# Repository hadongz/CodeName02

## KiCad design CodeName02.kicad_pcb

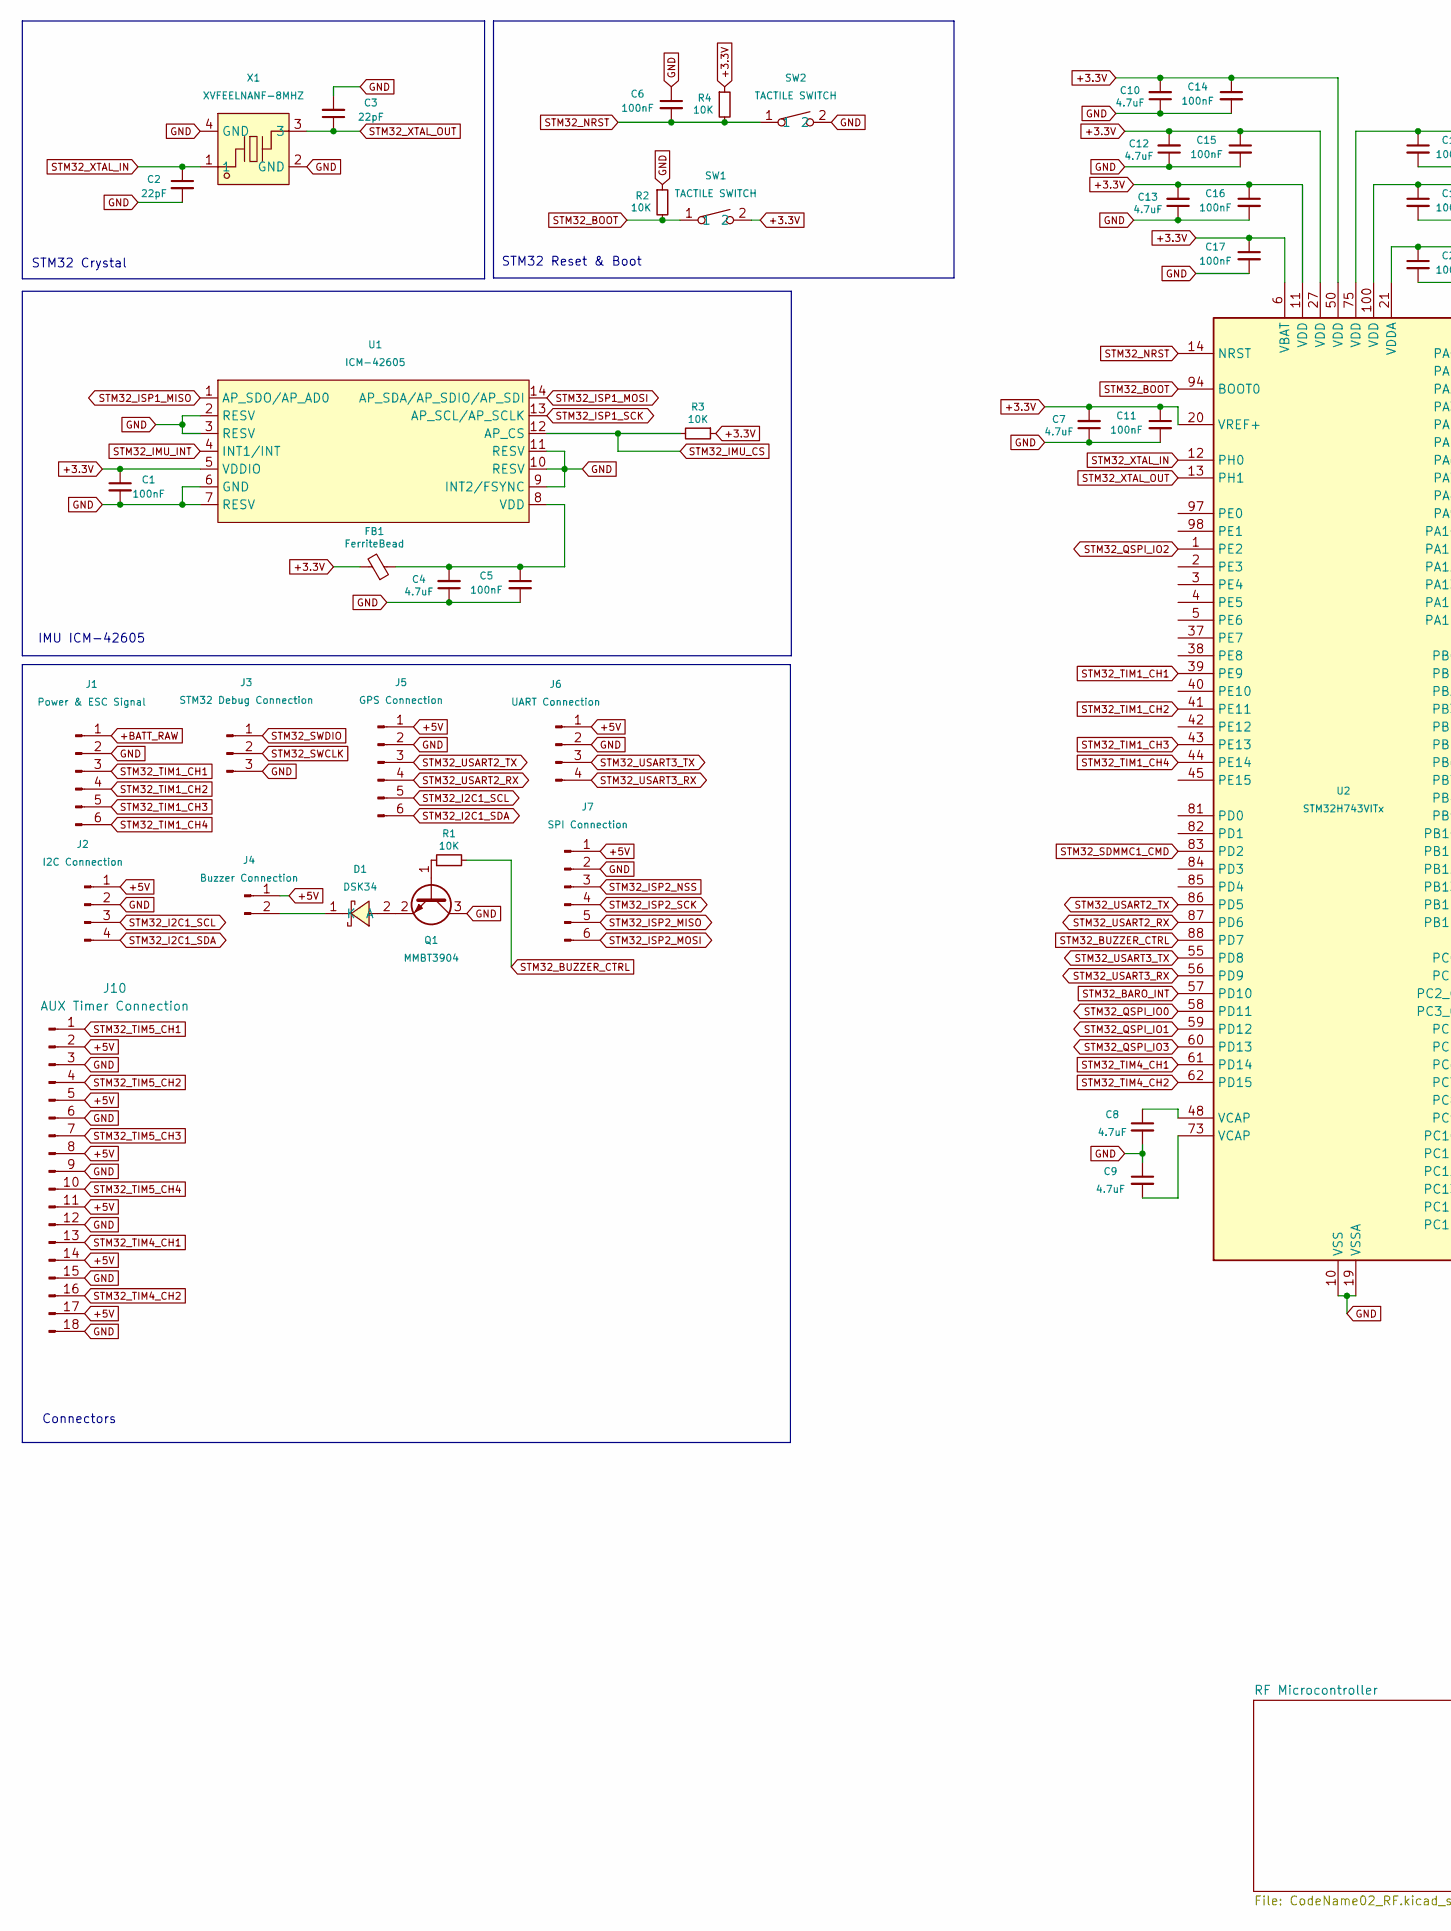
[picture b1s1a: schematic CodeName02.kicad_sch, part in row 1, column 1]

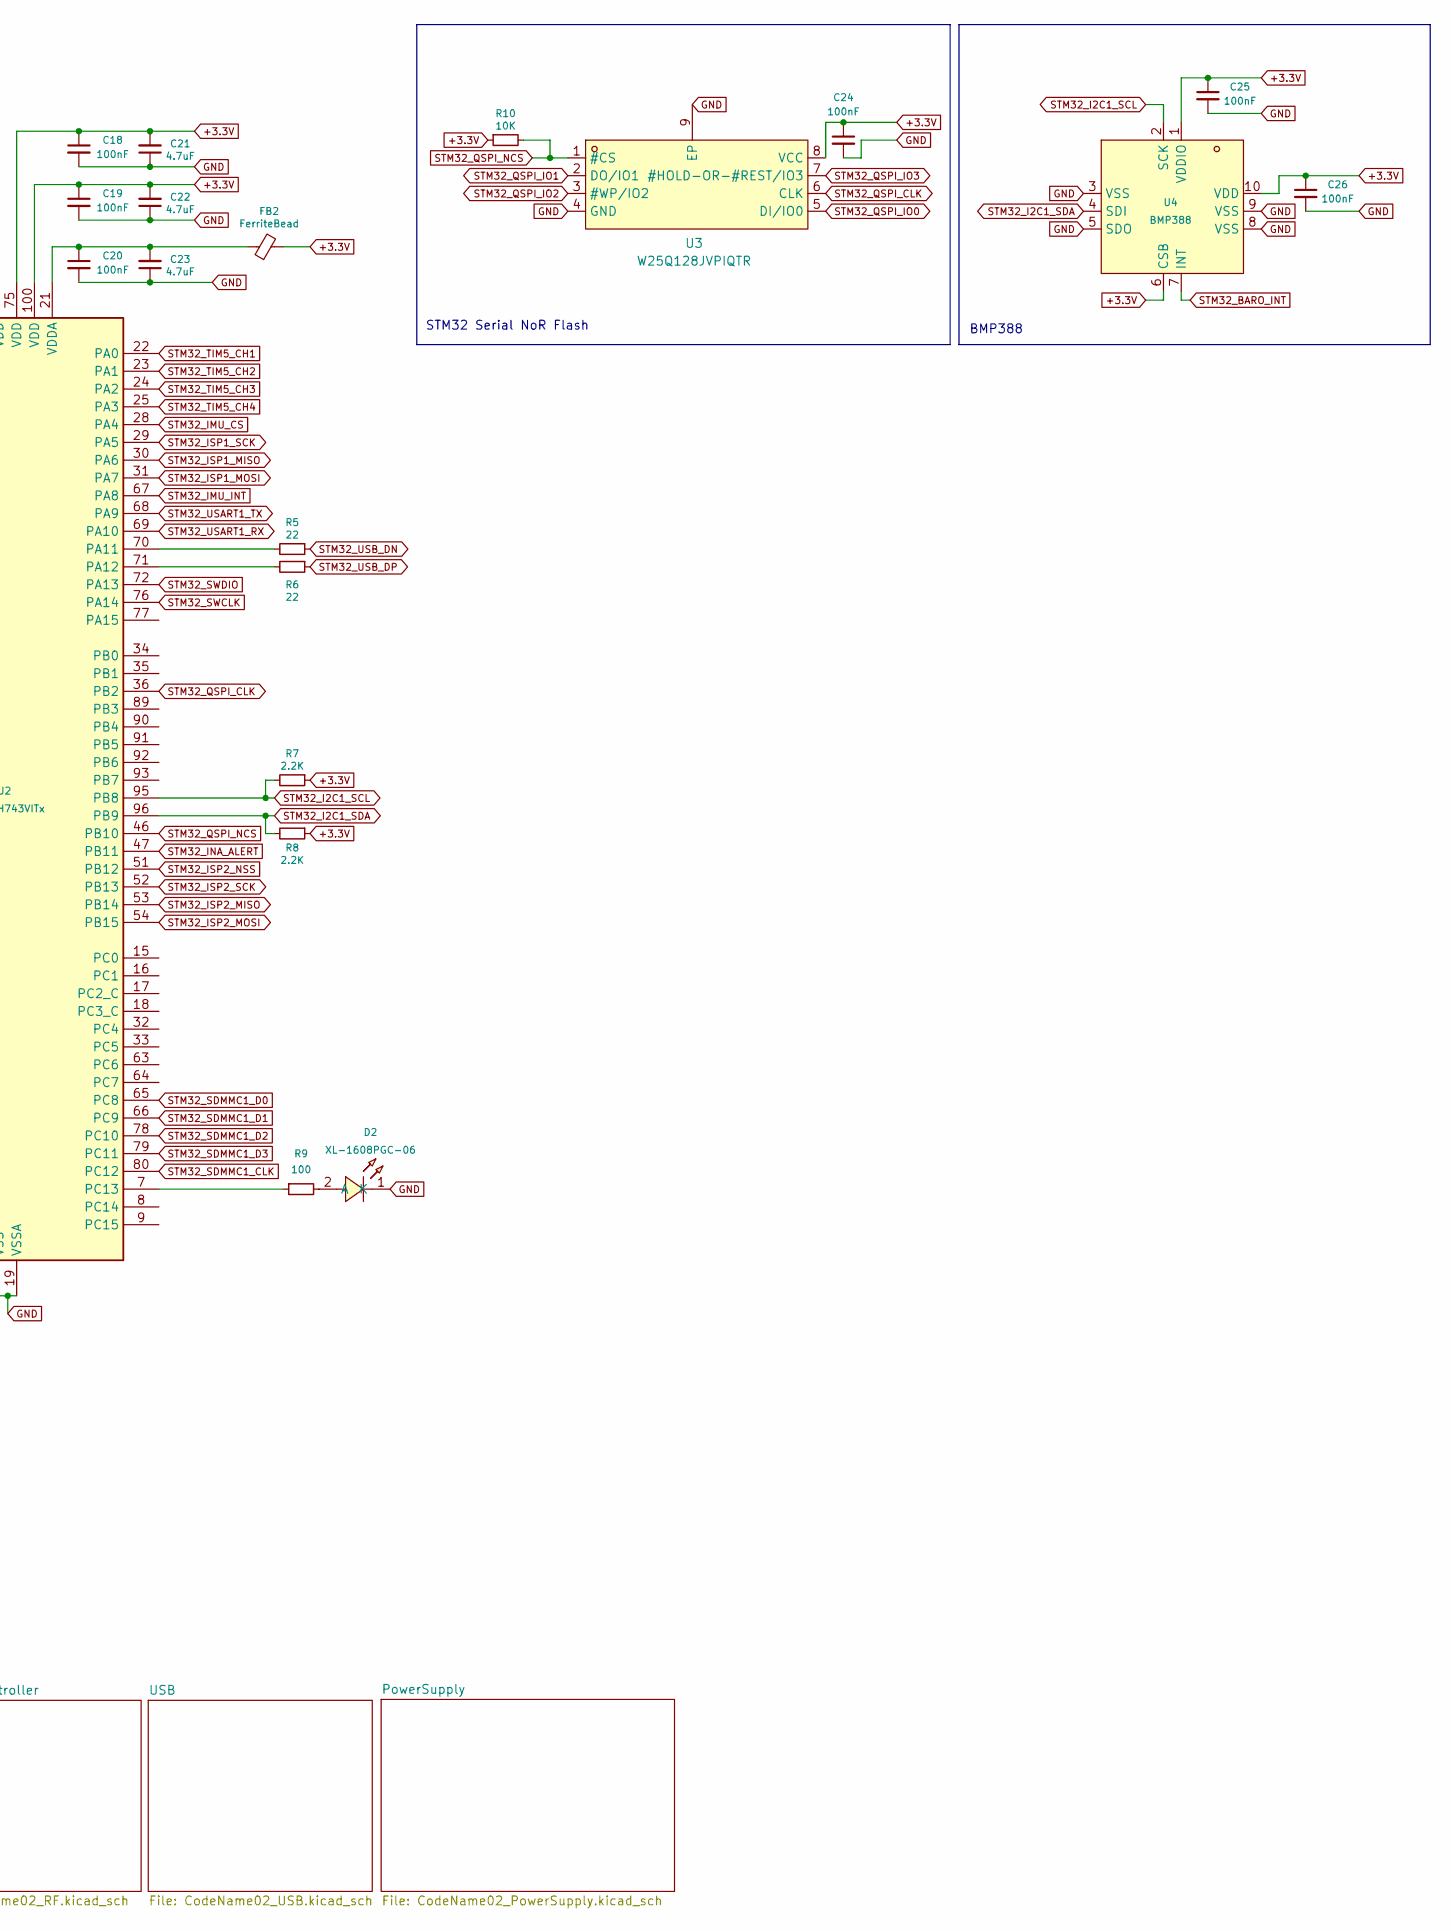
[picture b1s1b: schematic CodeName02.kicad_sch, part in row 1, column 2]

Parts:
C1, C5, C6, C11, C14, C15, C16, C17, C18, C19, C20, C24, C25, C26: 100nF; C_0603_1608Metric
C2, C3: 22pF; C_0603_1608Metric
C4, C7, C8, C9, C10, C12, C13, C21, C22, C23: 4.7uF; C_0603_1608Metric
D1: DSK34; SOD-123FL_L2.7-W1.8-LS3.8-RD; LCSC Part C727076
D2: XL-1608PGC-06; LED0603-RD_GREEN; LCSC Part C7371905
FB1, FB2: FerriteBead; L_0603_1608Metric
J1: Power & ESC Signal; JST_GH_SM06B-GHS-TB_1x06-1MP_P1.25mm_Horizontal
J2: I2C Connection; JST_GH_BM04B-GHS-TBT_1x04-1MP_P1.25mm_Vertical
J3: STM32 Debug Connection; PinHeader_1x03_P2.54mm_Vertical_Custom
J4: Buzzer Connection; JST_GH_SM02B-GHS-TB_1x02-1MP_P1.25mm_Horizontal
J5: GPS Connection; JST_GH_SM06B-GHS-TB_1x06-1MP_P1.25mm_Horizontal
J6: UART Connection; JST_GH_SM04B-GHS-TB_1x04-1MP_P1.25mm_Horizontal
J7: SPI Connection; JST_GH_SM06B-GHS-TB_1x06-1MP_P1.25mm_Horizontal
J10: AUX Timer Connection; PinHeader_3Row_Custom
Q1: MMBT3904; SOT-23
R1, R2, R3, R4, R10: 10K; R_0603_1608Metric
R5, R6: 22; R_0603_1608Metric
R7, R8: 2.2K; R_0603_1608Metric
R9: 100; R_0603_1608Metric
SW1, SW2: TACTILE SWITCH; KEY-SMD_L4.0-W3.0-LS4.9-1; LCSC Part C49234124
U1: ICM-42605; LGA-14_L3.0-W2.5-P0.50-TL; LCSC Part C2655099
U2: STM32H743VITx; LQFP-100_14x14mm_P0.5mm
U3: W25Q128JVPIQTR; WSON-8_L6.0-W5.0-P1.27-BL; LCSC Part C190862
U4: BMP388; SENSORM-SMD_BMP388; LCSC Part C779278
X1: XVFEELNANF-8MHZ; CRYSTAL-SMD_4P-L5.0-W3.2-BL-1; LCSC Part C5160132

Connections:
+3.3V: C1.1, C7.2, C10.2, C11.1, C12.2, C13.2, C14.1, C15.1, C16.1, C17.1, C18.1, C19.1, C21.2, C22.2, C24.1, C25.1, C26.1, FB1.2, FB2.2, R3.1, R4.1, R7.1, R8.1, R10.1, SW1.2, U1.5 (VDDIO), U2.6 (VBAT), U2.11 (VDD), U2.20 (VREF+), U2.27 (VDD), U2.50 (VDD), U2.75 (VDD), U2.100 (VDD), U3.8 (VCC), U4.1 (VDDIO), U4.6 (CSB), U4.10 (VDD); also elsewhere on the board
+5V: J2.1, J4.1, J5.1, J6.1, J7.1, J10.2, J10.5, J10.8, J10.11, J10.14, J10.17; also elsewhere on the board
+BATT_RAW: J1.1; also elsewhere on the board
GND: C1.2, C2.2, C3.2, C4.1, C5.2, C6.1, C7.1, C8.2, C9.1, C10.1, C11.2, C12.1, C13.1, C14.2, C15.2, C16.2, C17.2, C18.2, C19.2, C20.2, C21.1, C22.1, C23.1, C24.2, C25.2, C26.2, D2.1 (K), J1.2, J1.MP, J2.2, J3.3, J4.MP, J5.2, J5.MP, J6.2, J6.MP, J7.2, J7.MP, J10.3, J10.6, J10.9, J10.12, J10.15, J10.18, Q1.3 (C), R2.1, SW2.2, U1.2 (RESV), U1.3 (RESV), U1.6 (GND), U1.7 (RESV), U1.9 (INT2/FSYNC), U1.10 (RESV), U1.11 (RESV), U2.10 (VSS), U2.19 (VSSA), U2.26 (VSS), U2.49 (VSS), U2.74 (VSS), U2.99 (VSS), U3.4 (GND), U3.9 (EP), U4.3 (VSS), U4.5 (SDO), U4.8 (VSS), U4.9 (VSS), X1.2 (GND), X1.4 (GND); also elsewhere on the board
unnamed: C8.1, U2.48 (VCAP)
unnamed: C9.2, U2.73 (VCAP)
unnamed: D1.2 (A), Q1.2 (E)
unnamed: D1.1 (K), J4.2
unnamed: D2.2 (A), R9.2
unnamed: Q1.1 (B), R1.1
unnamed: C4.2, C5.1, FB1.1, U1.8 (VDD)
unnamed: R5.2, U2.70 (PA11)
unnamed: R6.2, U2.71 (PA12)
unnamed: R9.1, U2.7 (PC13)
unnamed: C20.1, C23.2, FB2.1, U2.21 (VDDA)
STM32_BARO_INT: U2.57 (PD10), U4.7 (INT)
STM32_BOOT: R2.2, SW1.1, U2.94 (BOOT0)
STM32_BUZZER_CTRL: R1.2, U2.88 (PD7)
STM32_I2C1_SCL: J2.3, J5.5, R7.2, U2.95 (PB8), U4.2 (SCK); also elsewhere on the board
STM32_I2C1_SDA: J2.4, J5.6, R8.2, U2.96 (PB9), U4.4 (SDI); also elsewhere on the board
STM32_IMU_CS: R3.2, U1.12 (AP_CS), U2.28 (PA4)
STM32_IMU_INT: U1.4 (INT1/INT), U2.67 (PA8)
STM32_INA_ALERT: U2.47 (PB11); also elsewhere on the board
STM32_ISP1_MISO: U1.1 (AP_SDO/AP_AD0), U2.30 (PA6)
STM32_ISP1_MOSI: U1.14 (AP_SDA/AP_SDIO/AP_SDI), U2.31 (PA7)
STM32_ISP1_SCK: U1.13 (AP_SCL/AP_SCLK), U2.29 (PA5)
STM32_ISP2_MISO: J7.5, U2.53 (PB14)
STM32_ISP2_MOSI: J7.6, U2.54 (PB15)
STM32_ISP2_NSS: J7.3, U2.51 (PB12)
STM32_ISP2_SCK: J7.4, U2.52 (PB13)
STM32_NRST: C6.2, R4.2, SW2.1, U2.14 (NRST)
STM32_QSPI_CLK: U2.36 (PB2), U3.6 (CLK)
STM32_QSPI_IO0: U2.58 (PD11), U3.5 (DI/IO0)
STM32_QSPI_IO1: U2.59 (PD12), U3.2 (DO/IO1)
STM32_QSPI_IO2: U2.1 (PE2), U3.3 (#WP/IO2)
STM32_QSPI_IO3: U2.60 (PD13), U3.7 (#HOLD-OR-#REST/IO3)
STM32_QSPI_NCS: R10.2, U2.46 (PB10), U3.1 (#CS)
STM32_SDMMC1_CLK: U2.80 (PC12)
STM32_SDMMC1_CMD: U2.83 (PD2)
STM32_SDMMC1_D0: U2.65 (PC8)
STM32_SDMMC1_D1: U2.66 (PC9)
STM32_SDMMC1_D2: U2.78 (PC10)
STM32_SDMMC1_D3: U2.79 (PC11)
STM32_SWCLK: J3.2, U2.76 (PA14)
STM32_SWDIO: J3.1, U2.72 (PA13)
STM32_TIM1_CH1: J1.3, U2.39 (PE9)
STM32_TIM1_CH2: J1.4, U2.41 (PE11)
STM32_TIM1_CH3: J1.5, U2.43 (PE13)
STM32_TIM1_CH4: J1.6, U2.44 (PE14)
STM32_TIM4_CH1: J10.13, U2.61 (PD14)
STM32_TIM4_CH2: J10.16, U2.62 (PD15)
STM32_TIM5_CH1: J10.1, U2.22 (PA0)
STM32_TIM5_CH2: J10.4, U2.23 (PA1)
STM32_TIM5_CH3: J10.7, U2.24 (PA2)
STM32_TIM5_CH4: J10.10, U2.25 (PA3)
STM32_USART1_RX: U2.69 (PA10); also elsewhere on the board
STM32_USART1_TX: U2.68 (PA9); also elsewhere on the board
STM32_USART2_RX: J5.4, U2.87 (PD6)
STM32_USART2_TX: J5.3, U2.86 (PD5)
STM32_USART3_RX: J6.4, U2.56 (PD9)
STM32_USART3_TX: J6.3, U2.55 (PD8)
STM32_USB_DN: R5.1; also elsewhere on the board
STM32_USB_DP: R6.1; also elsewhere on the board
STM32_XTAL_IN: C2.1, U2.12 (PH0), X1.1
STM32_XTAL_OUT: C3.1, U2.13 (PH1), X1.3

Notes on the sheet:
STM32 Crystal
STM32 Reset & Boot
Connectors
BMP388
STM32 Serial NoR Flash
IMU ICM-42605

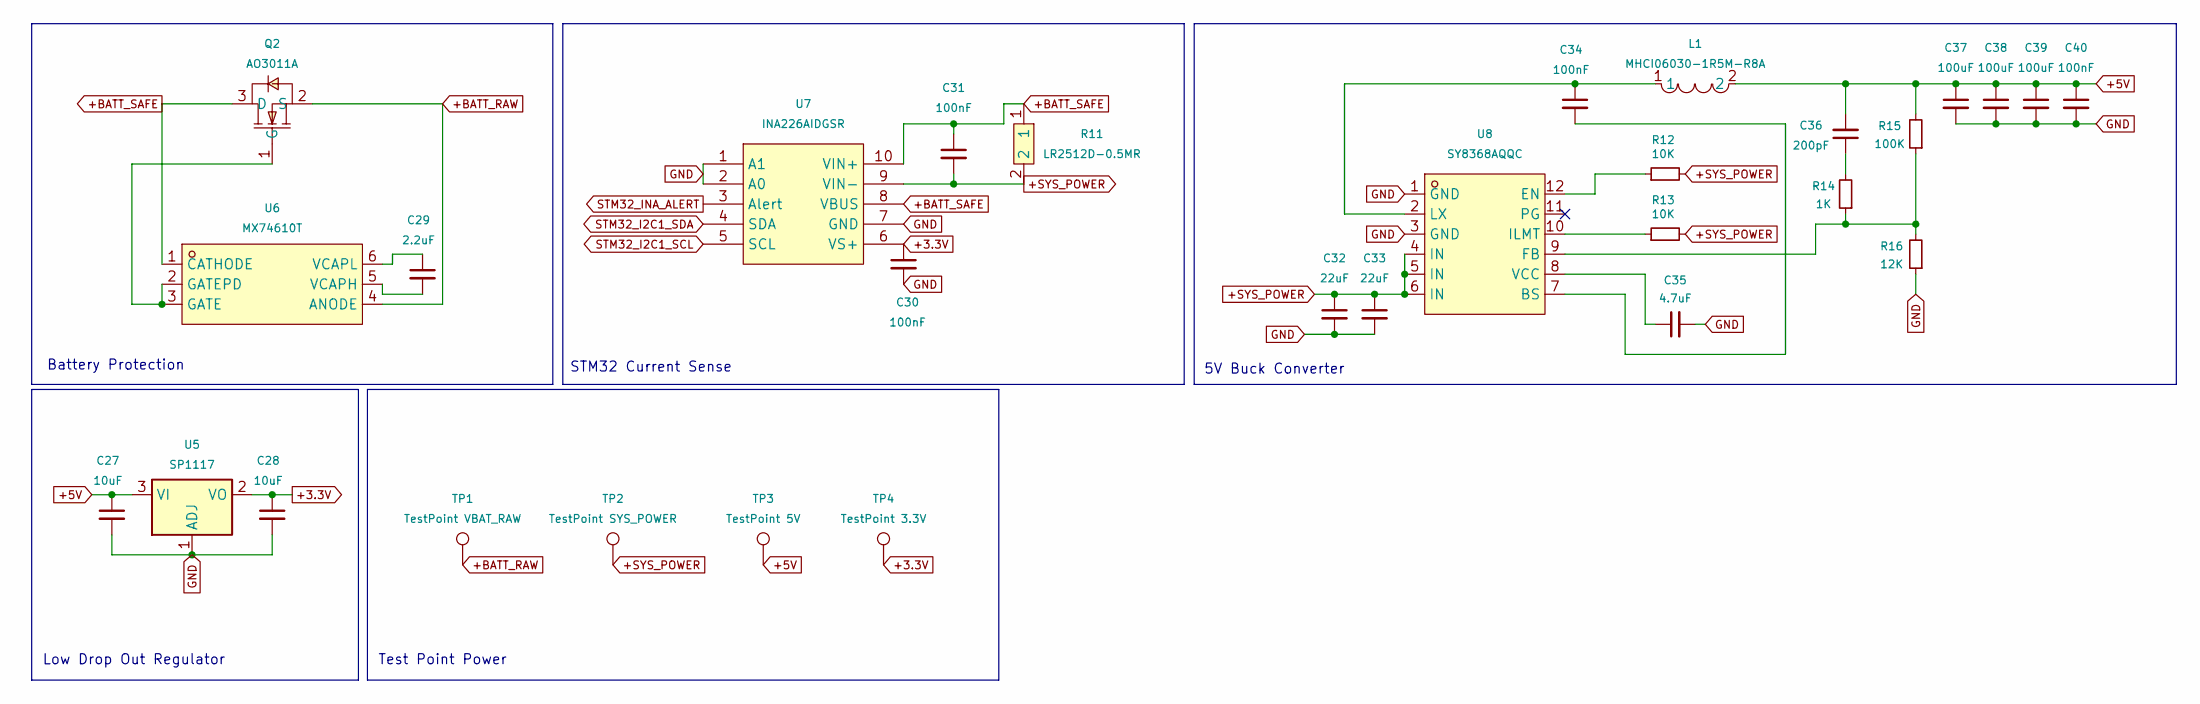
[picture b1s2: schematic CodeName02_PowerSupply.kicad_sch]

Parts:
C27, C28: 10uF; C_0805_2012Metric
C29: 2.2uF; C_0603_1608Metric
C30, C31, C34, C40: 100nF; C_0603_1608Metric
C32, C33: 22uF; C_0805_2012Metric
C35: 4.7uF; C_0603_1608Metric
C36: 200pF; C_0603_1608Metric
C37, C38, C39: 100uF; C_1206_3216Metric
L1: MHCI06030-1R5M-R8A; IND-SMD_L7.3-W6.6; LCSC Part C329386
Q2: AO3011A; SOT-23-3_L2.9-W1.6-P1.90-LS2.8-BR; LCSC Part C49046454
R11: LR2512D-0.5MR; RES-SMD_L6.4-W3.2_C500733; LCSC Part C500733
R12, R13: 10K; R_0603_1608Metric
R14: 1K; R_0603_1608Metric
R15: 100K; R_0603_1608Metric
R16: 12K; R_0603_1608Metric
TP1: TestPoint VBAT_RAW; TestPoint_Pad_D2.0mm
TP2: TestPoint SYS_POWER; TestPoint_Pad_D2.0mm
TP3: TestPoint 5V; TestPoint_Pad_D2.0mm
TP4: TestPoint 3.3V; TestPoint_Pad_D2.0mm
U5: SP1117; SOT-223-3_TabPin2
U6: MX74610T; SOT-23-6_L2.9-W1.6-P0.95-LS2.8-BL-1; LCSC Part C19078229
U7: INA226AIDGSR; MSOP-10_L3.0-W3.0-P0.50-LS5.0-BL; LCSC Part C49851
U8: SY8368AQQC; QFN-12_L3.0-W3.0-P0.45-TL-EP; LCSC Part C207642

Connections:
+3.3V: C28.1, C30.1, TP4.1, U5.2 (VO), U7.6 (VS+); also elsewhere on the board
+5V: C27.1, C36.2, C37.1, C38.1, C39.1, C40.1, L1.2, R15.2, TP3.1, U5.3 (VI); also elsewhere on the board
+BATT_RAW: Q2.2 (S), TP1.1, U6.4 (ANODE); also elsewhere on the board
+BATT_SAFE: C31.1, Q2.3 (D), R11.1, U6.1 (CATHODE), U7.8 (VBUS), U7.10 (VIN+)
+SYS_POWER: C31.2, C32.1, C33.1, R11.2, R12.2, R13.2, TP2.1, U7.9 (VIN-), U8.4 (IN), U8.5 (IN), U8.6 (IN); also elsewhere on the board
GND: C27.2, C28.2, C30.2, C32.2, C33.2, C35.2, C37.2, C38.2, C39.2, C40.2, R16.1, U5.1 (ADJ), U7.1 (A1), U7.2 (A0), U7.7 (GND), U8.1 (GND), U8.3 (GND); also elsewhere on the board
unnamed: C36.1, R14.2
unnamed: Q2.1 (G), U6.2 (GATEPD), U6.3 (GATE)
unnamed: C29.2, U6.5 (VCAPH)
unnamed: C29.1, U6.6 (VCAPL)
unnamed: C34.2, U8.7 (BS)
unnamed: R12.1, U8.12 (EN)
unnamed: R14.1, R15.1, R16.2, U8.9 (FB)
unnamed: R13.1, U8.10 (ILMT)
unnamed: C34.1, L1.1, U8.2 (LX)
unnamed: C35.1, U8.8 (VCC)
STM32_I2C1_SCL: U7.5 (SCL); also elsewhere on the board
STM32_I2C1_SDA: U7.4 (SDA); also elsewhere on the board
STM32_INA_ALERT: U7.3 (Alert); also elsewhere on the board

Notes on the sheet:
Low Drop Out Regulator
Test Point Power
Battery Protection
5V Buck Converter
STM32 Current Sense

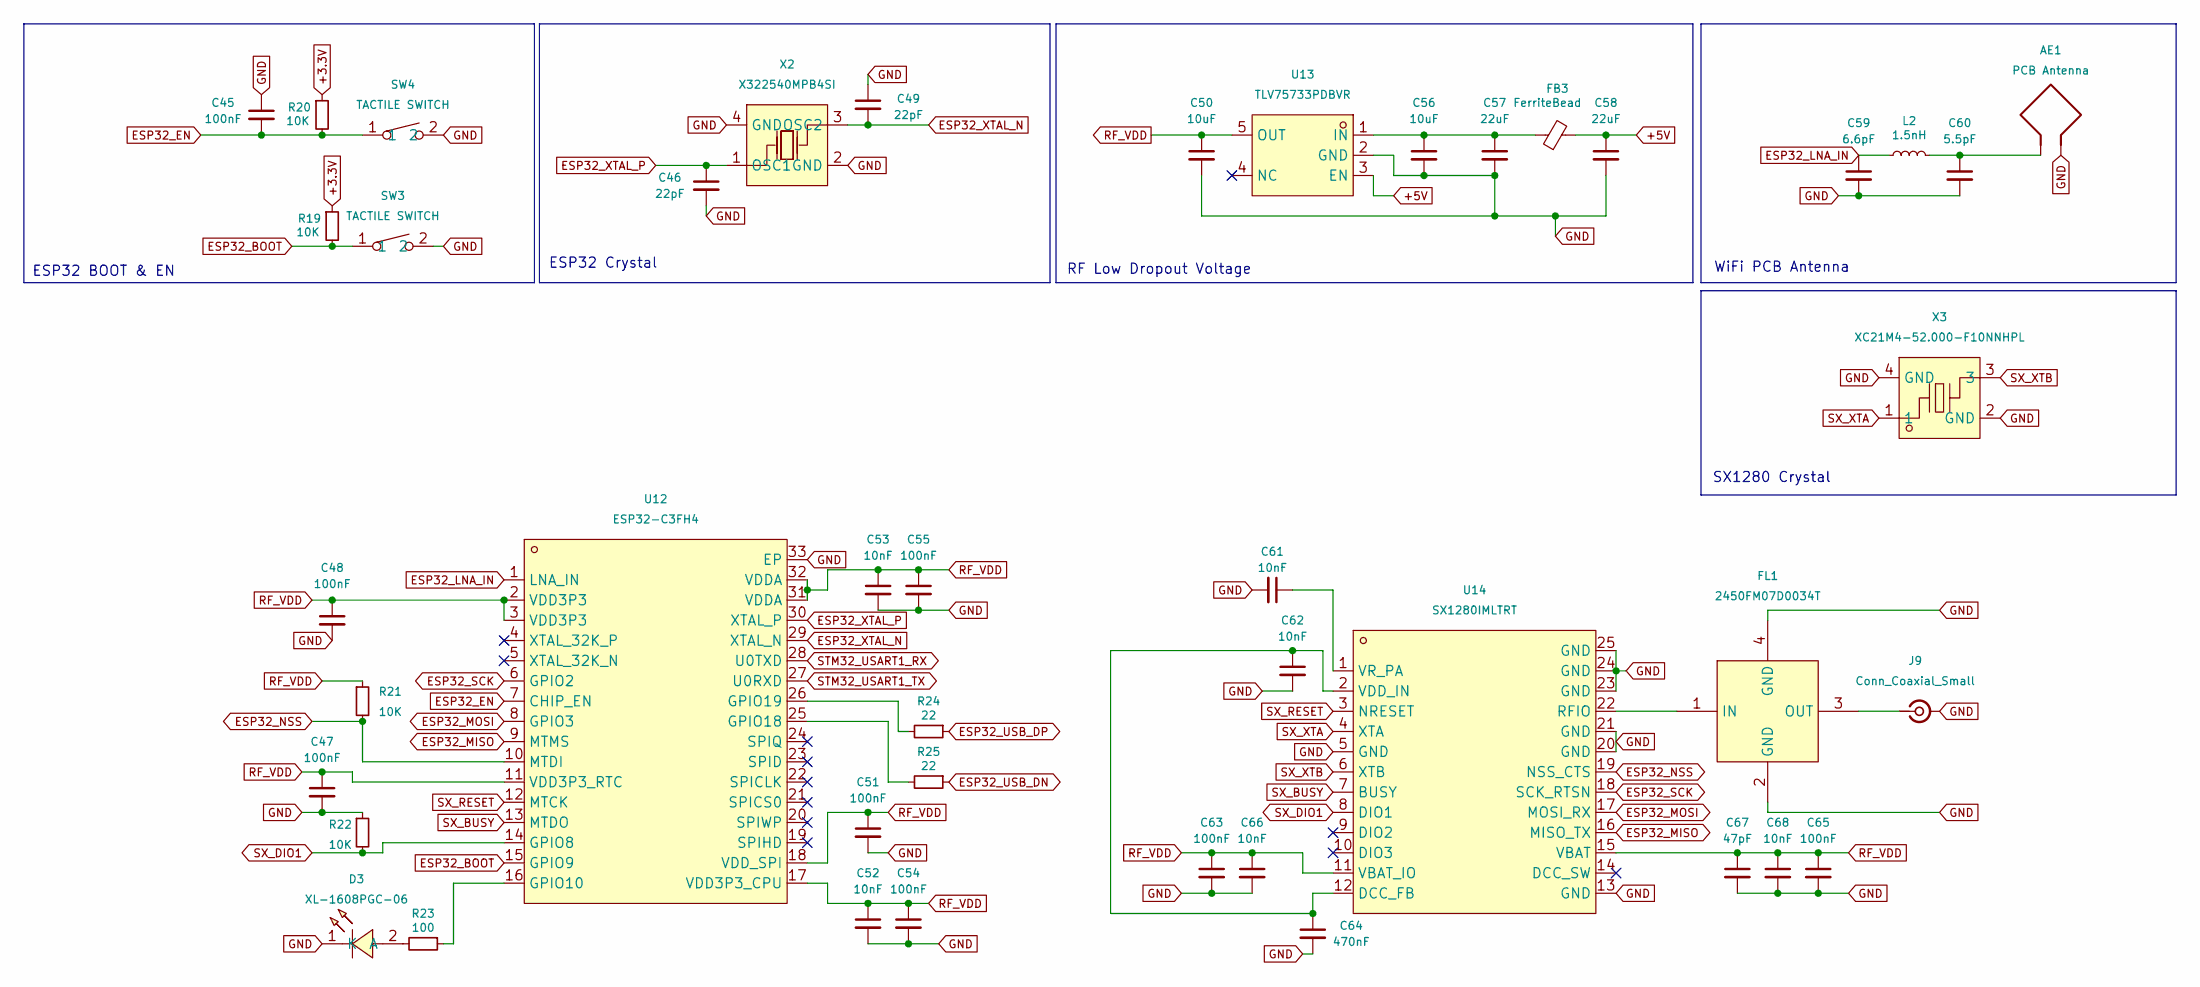
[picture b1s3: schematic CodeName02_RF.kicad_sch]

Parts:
AE1: PCB Antenna; Texas_SWRA117D_2.4GHz_Right
C45, C47, C48, C51, C54, C55, C63, C65: 100nF; C_0603_1608Metric
C46, C49: 22pF; C_0603_1608Metric
C50, C56: 10uF; C_0603_1608Metric
C52, C53, C61, C62, C66, C68: 10nF; C_0603_1608Metric
C57, C58: 22uF; C_0603_1608Metric
C59: 6.6pF; C_0402_1005Metric
C60: 5.5pF; C_0402_1005Metric
C64: 470nF; C_0603_1608Metric
C67: 47pF; C_0402_1005Metric
D3: XL-1608PGC-06; LED0603-RD_GREEN; LCSC Part C7371905
FB3: FerriteBead; L_0603_1608Metric
FL1: 2450FM07D0034T; FILTER-SMD_4P-L1.0-W0.5-L; LCSC Part C2651081
J9: Conn_Coaxial_Small; U.FL_Hirose_U.FL-R-SMT-1_Vertical
L2: 1.5nH; L_0402_1005Metric
R19, R20, R21, R22: 10K; R_0603_1608Metric
R23: 100; R_0603_1608Metric
R24, R25: 22; R_0603_1608Metric
SW3, SW4: TACTILE SWITCH; KEY-SMD_L4.0-W3.0-LS4.9-1; LCSC Part C49234124
U12: ESP32-C3FH4; QFN-32_L5.0-W5.0-P0.50-TL-EP3.7; LCSC Part C2858491
U13: TLV75733PDBVR; SOT-23-5_L2.9-W1.6-P0.95-LS2.8-BL; LCSC Part C485517
U14: SX1280IMLTRT; QFN-24_L4.0-W4.0-P0.50-BL-EP2.6; LCSC Part C125969
X2: X322540MPB4SI; OSC-SMD_4P-L3.2-W2.5-BL_SIT8008BI; LCSC Part C9010
X3: XC21M4-52.000-F10NNHPL; CRYSTAL-SMD_4P-L2.0-W1.6-BL; LCSC Part C3034316

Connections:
+3.3V: R19.1, R20.1; also elsewhere on the board
+5V: C58.1, FB3.2, U13.3 (EN); also elsewhere on the board
ESP32_BOOT: R19.2, SW3.1, U12.15 (GPIO9)
ESP32_EN: C45.2, R20.2, SW4.1, U12.7 (CHIP_EN)
ESP32_LNA_IN: C59.1, L2.1, U12.1 (LNA_IN)
ESP32_MISO: U12.9 (MTMS), U14.16 (MISO_TX)
ESP32_MOSI: U12.8 (GPIO3), U14.17 (MOSI_RX)
ESP32_NSS: R21.2, U12.10 (MTDI), U14.19 (NSS_CTS)
ESP32_SCK: U12.6 (GPIO2), U14.18 (SCK_RTSN)
ESP32_USB_DN: R25.1; also elsewhere on the board
ESP32_USB_DP: R24.1; also elsewhere on the board
ESP32_XTAL_N: C49.2, U12.29 (XTAL_N), X2.3 (OSC2)
ESP32_XTAL_P: C46.1, U12.30 (XTAL_P), X2.1 (OSC1)
GND: AE1.2, C45.1, C46.2, C47.2, C48.2, C49.1, C50.2, C51.2, C52.2, C53.2, C54.2, C55.2, C56.2, C57.2, C58.2, C59.2, C60.2, C61.2, C62.2, C63.2, C64.2, C65.2, C66.2, C67.2, C68.2, D3.1 (K), FL1.2 (GND), FL1.4 (GND), J9.2 (Ext), R22.1, SW3.2, SW4.2, U12.33 (EP), U13.2 (GND), U14.5 (GND), U14.13 (GND), U14.20 (GND), U14.21 (GND), U14.23 (GND), U14.24 (GND), U14.25 (GND), X2.2 (GND), X2.4 (GND), X3.2 (GND), X3.4 (GND); also elsewhere on the board
unnamed: AE1.1, C60.1, L2.2
unnamed: D3.2 (A), R23.2
unnamed: FL1.1 (IN), U14.22 (RFIO)
unnamed: FL1.3 (OUT), J9.1 (In)
unnamed: R23.1, U12.16 (GPIO10)
unnamed: R25.2, U12.25 (GPIO18)
unnamed: R24.2, U12.26 (GPIO19)
unnamed: C56.1, C57.1, FB3.1, U13.1 (IN)
unnamed: C62.1, C64.1, U14.2 (VDD_IN), U14.12 (DCC_FB)
unnamed: C61.1, U14.1 (VR_PA)
RF_VDD: C47.1, C48.1, C50.1, C51.1, C52.1, C53.1, C54.1, C55.1, C63.1, C65.1, C66.1, C67.1, C68.1, R21.1, U12.2 (VDD3P3), U12.3 (VDD3P3), U12.11 (VDD3P3_RTC), U12.17 (VDD3P3_CPU), U12.18 (VDD_SPI), U12.31 (VDDA), U12.32 (VDDA), U13.5 (OUT), U14.11 (VBAT_IO), U14.15 (VBAT)
STM32_USART1_RX: U12.28 (U0TXD); also elsewhere on the board
STM32_USART1_TX: U12.27 (U0RXD); also elsewhere on the board
SX_BUSY: U12.13 (MTDO), U14.7 (BUSY)
SX_DIO1: R22.2, U12.14 (GPIO8), U14.8 (DIO1)
SX_RESET: U12.12 (MTCK), U14.3 (NRESET)
SX_XTA: U14.4 (XTA), X3.1
SX_XTB: U14.6 (XTB), X3.3

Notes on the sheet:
ESP32 BOOT & EN
RF Low Dropout Voltage
ESP32 Crystal
SX1280 Crystal
WiFi PCB Antenna

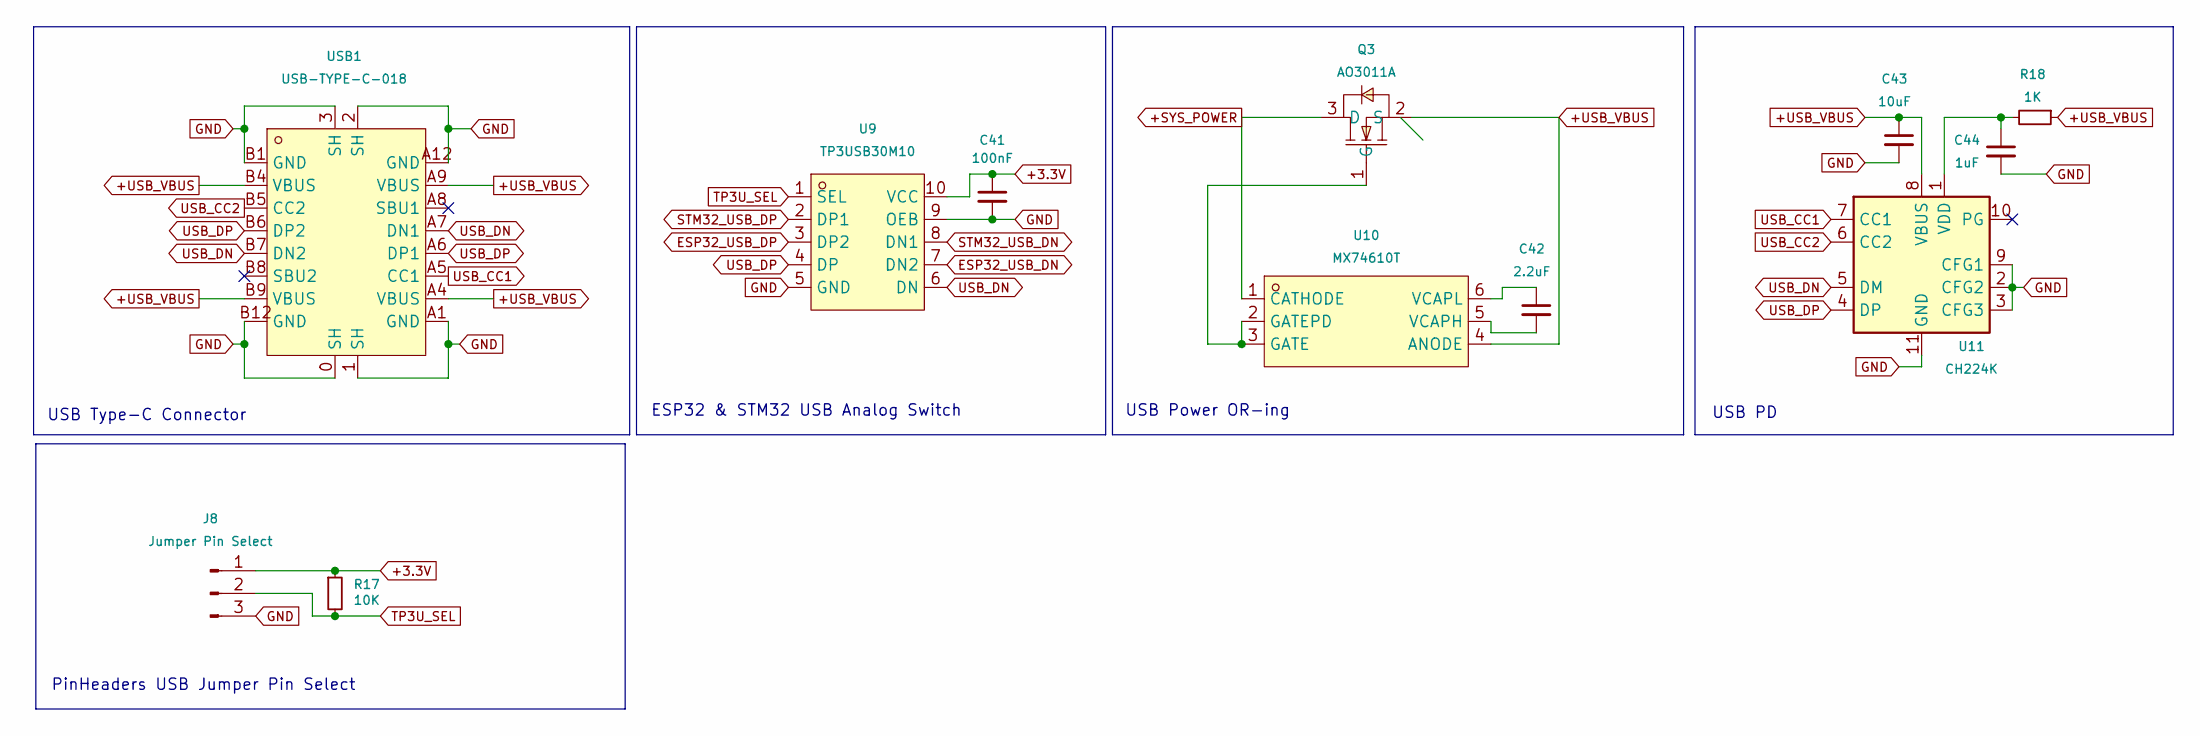
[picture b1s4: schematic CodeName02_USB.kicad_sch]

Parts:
C41: 100nF; C_0603_1608Metric
C42: 2.2uF; C_0603_1608Metric
C43: 10uF; C_0805_2012Metric
C44: 1uF; C_0603_1608Metric
J8: Jumper Pin Select; PinHeader_1x03_P2.54mm_Vertical_Custom
Q3: AO3011A; SOT-23-3_L2.9-W1.6-P1.90-LS2.8-BR; LCSC Part C49046454
R17: 10K; R_0603_1608Metric
R18: 1K; R_0603_1608Metric
U9: TP3USB30M10; MSOP-10_L3.0-W3.0-P0.50-LS4.9-BL; LCSC Part C2959840
U10: MX74610T; SOT-23-6_L2.9-W1.6-P0.95-LS2.8-BL-1; LCSC Part C19078229
U11: CH224K; SSOP-10-1EP_3.9x4.9mm_P1mm_EP2.1x3.3mm
USB1: USB-TYPE-C-018; USB-C_SMD-TYPE-C-31-M-12; LCSC Part C2927038

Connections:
+3.3V: C41.1, J8.1, R17.1, U9.10 (VCC); also elsewhere on the board
+SYS_POWER: Q3.3 (D), U10.1 (CATHODE); also elsewhere on the board
+USB_VBUS: C43.1, Q3.2 (S), R18.1, U10.4 (ANODE), U11.8 (VBUS), USB1.A4 (VBUS), USB1.A9 (VBUS), USB1.B4 (VBUS), USB1.B9 (VBUS)
ESP32_USB_DN: U9.7 (DN2); also elsewhere on the board
ESP32_USB_DP: U9.3 (DP2); also elsewhere on the board
GND: C41.2, C43.2, C44.2, J8.3, U9.5 (GND), U9.9 (OEB), U11.2 (CFG2), U11.3 (CFG3), U11.9 (CFG1), U11.11 (GND), USB1.0 (SH), USB1.1 (SH), USB1.2 (SH), USB1.3 (SH), USB1.A1 (GND), USB1.A12 (GND), USB1.B1 (GND), USB1.B12 (GND); also elsewhere on the board
unnamed: Q3.1 (G), U10.2 (GATEPD), U10.3 (GATE)
unnamed: C42.2, U10.5 (VCAPH)
unnamed: C42.1, U10.6 (VCAPL)
unnamed: C44.1, R18.2, U11.1 (VDD)
STM32_USB_DN: U9.8 (DN1); also elsewhere on the board
STM32_USB_DP: U9.2 (DP1); also elsewhere on the board
TP3U_SEL: J8.2, R17.2, U9.1 (SEL)
USB_CC1: U11.7 (CC1), USB1.A5 (CC1)
USB_CC2: U11.6 (CC2), USB1.B5 (CC2)
USB_DN: U9.6 (DN), U11.5 (DM), USB1.A7 (DN1), USB1.B7 (DN2)
USB_DP: U9.4 (DP), U11.4 (DP), USB1.A6 (DP1), USB1.B6 (DP2)

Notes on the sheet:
USB Power OR-ing
PinHeaders USB Jumper Pin Select
USB PD
ESP32 & STM32 USB Analog Switch
USB Type-C Connector

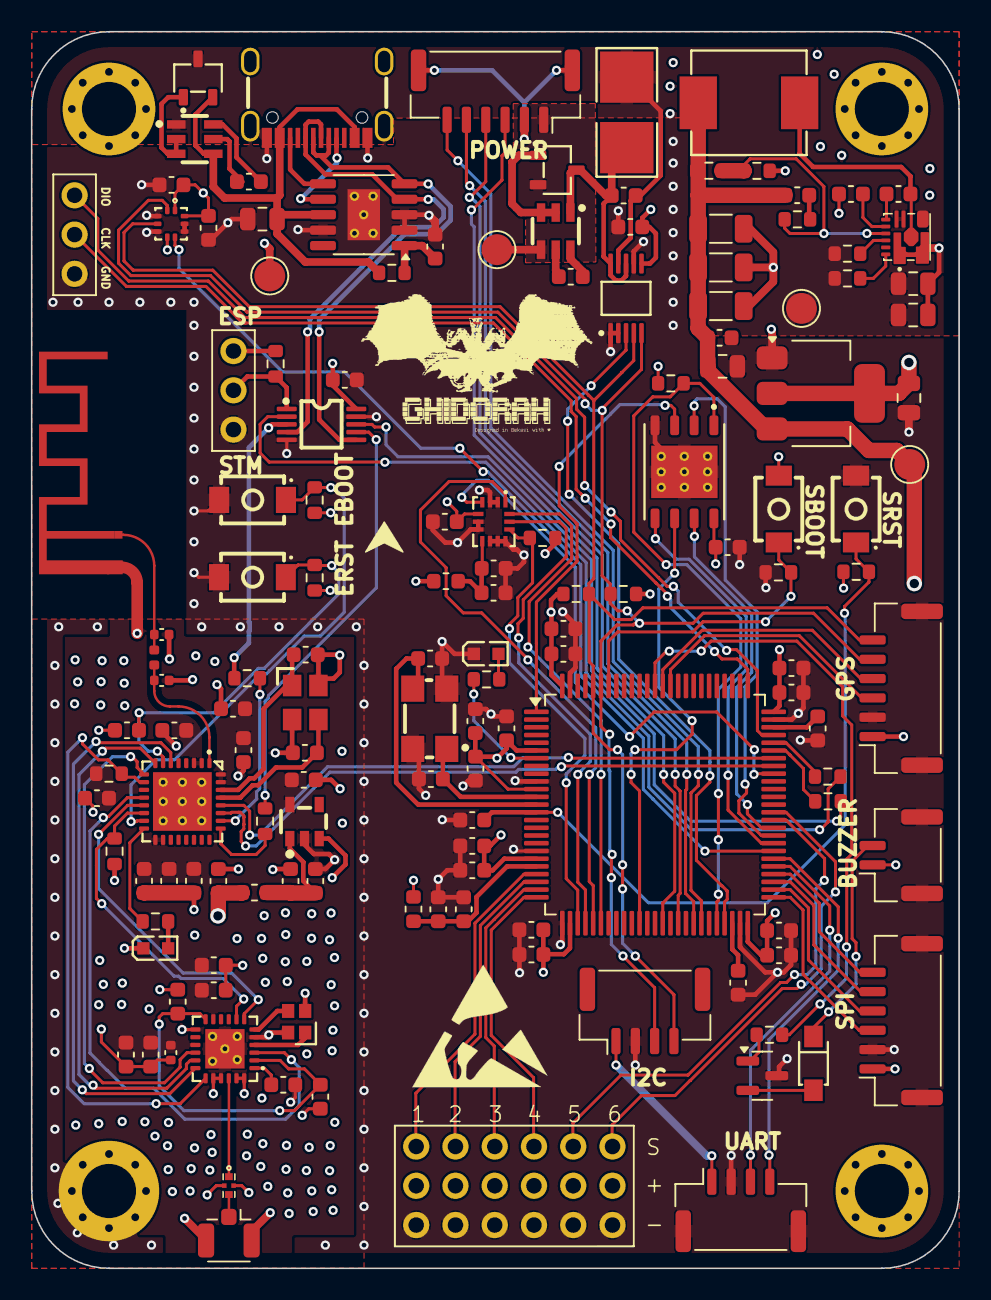
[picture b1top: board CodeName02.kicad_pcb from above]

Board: 4 copper layers, 60.0 x 80.0 mm, 142 parts (0 on the bottom side), 108 nets.

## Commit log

2025-10-06 [CodeName02] Initial Commit
2025-10-06 chore: add .gitignore
2025-10-06 fix: delete backups folder
2025-10-06 chore: delete zip
2025-10-06 feat: remove easykicad
2025-10-07 feat: schematic update
2025-10-07 feat: ESP32-C3 Antenna
2025-10-10 feat: finalize
